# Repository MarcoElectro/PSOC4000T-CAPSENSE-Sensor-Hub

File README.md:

# PSOC4000T-CAPSENSE-Sensor-Hub
An simple way to use capacitive sensors in combination with Infineon's CAPSENSE technology.

# Setup
After the PCB is soldered, the Rasperry Pi Pico needs to be connected as follows:
| Raspberry Pi Pico 2W Pin | Connection | Function |
|-----------------------|-----------------------|----------|
| GPIO2 (Pin 4)         | SDA (Sensor Hub)                | I2C Data |
| GPIO3 (Pin 5)         | SCL (Sensor Hub)                   | I2C Clock |
| GPIO28 (Pin 34)       | VCC (Sensor Hub)                  | Power Supply (3.3V) |
| GND (Pin 3 or 38)     | GND (Sensor Hub / BME280)                  | Ground |
| GPIO4 (Pin 6)         | BME280 SDA            | Environmental Sensor Data |
| GPIO5 (Pin 7)         | BME280 SCL 

# PicoLogger
For obtaining the CAPSENSE data from the Sensor Hub, the PicoLogger can be controlled over an web interface. 
Connect to the AP of the PicoLogger and call following pages:

- Main page: http://192.168.4.1
- Status page:  http://192.168.4.1/status

On the status page, the current state is shown e.g IDLE or the running data collection.

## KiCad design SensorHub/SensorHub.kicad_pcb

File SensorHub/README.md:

# KiCad Project for Sensor Hub PCB
The PCB conists of an PSOC4000T and a few additional components,
making the board a simple and cheap option to use Infineon`s CAPSENSE technology for capacitive sensors.

For programming an SWD Programmer is needed. 
I used the MiniProg4 (CY8CKIT-005-A).

Soldering the PSOC4000T is easy using solder paste and a heat plate or air soldering station.

Feel free to improve the layout and update it to your needs.

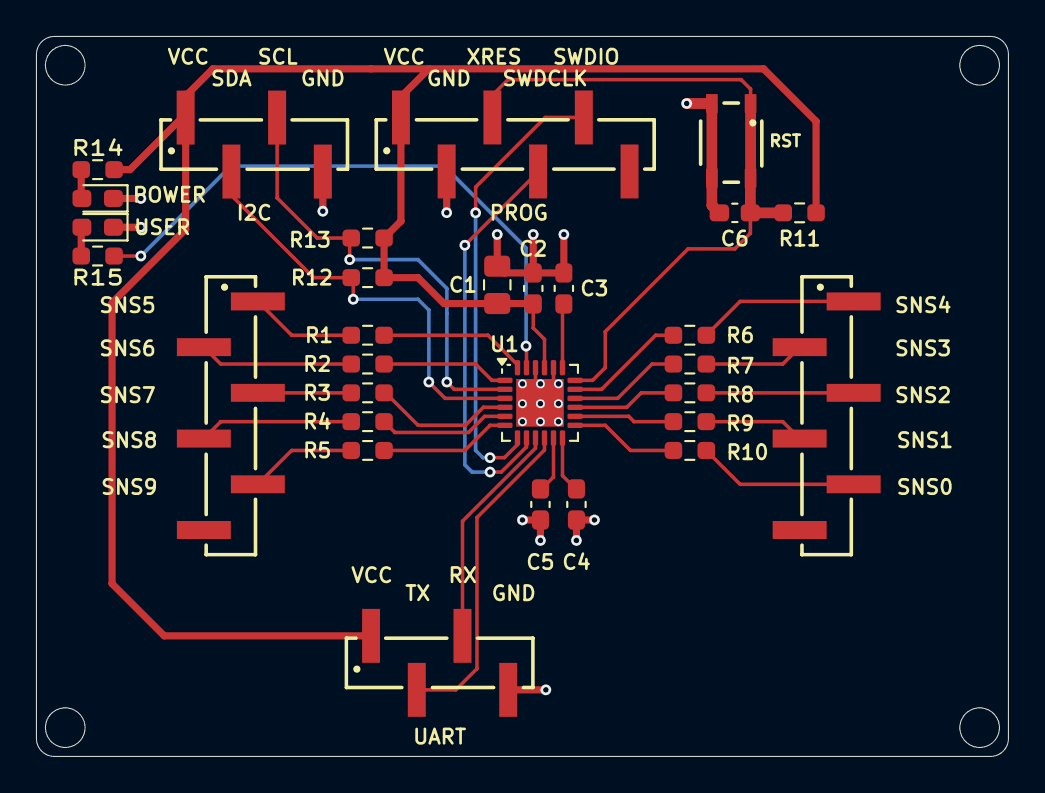
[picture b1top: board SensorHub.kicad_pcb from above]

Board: 2 copper layers, 54.0 x 40.0 mm, 30 parts (0 on the bottom side), 35 nets.

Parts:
C1: 4.7 µF; C_0805_2012Metric_Pad1.18x1.45mm_HandSolder
C2: 0.1 µF; C_0603_1608Metric_Pad1.08x0.95mm_HandSolder
C3: 2.2 µF; C_0603_1608Metric_Pad1.08x0.95mm_HandSolder
C4, C5: 2.2 nF; C_0603_1608Metric_Pad1.08x0.95mm_HandSolder
C6: 0.1µF; C_0603_1608Metric_Pad1.08x0.95mm_HandSolder
I2C: I2C; 61000418321_5pins
J1: CS1; 61000618321_6pins
J2: CS2; 61000618321_6pins
POWER: POWER; LED_0603_1608Metric_Pad1.05x0.95mm_HandSolder
PROG: SWD; 61000618321_6pins
R1, R2, R3, R4, R5, R6, R7, R8, R9, R10, R14: 560R; R_0603_1608Metric_Pad0.98x0.95mm_HandSolder
R11, R12, R13, R15: 4k7; R_0603_1608Metric_Pad0.98x0.95mm_HandSolder
RST: RESET; 434133025816
U1: CY8C4046LQI-T452; QFN-24-1EP_4x4mm_P0.5mm_EP2.65x2.65mm
UART: UART; 61000418321_5pins
USER: USER; LED_0603_1608Metric_Pad1.05x0.95mm_HandSolder

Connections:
/SCL: I2C.3, R13.2, U1.2 (P2.2)
/SDA: I2C.2, R12.2, U1.3 (P2.3)
/SNS0: R10.1, U1.13 (P0.0)
/SNS1: R9.1, U1.14 (P0.1)
/SNS2: R8.1, U1.15 (P0.2)
/SNS3: R7.1, U1.16 (P0.3)
/SNS4: R6.1, U1.17 (EXTCLK_P0.4)
/SNS5: R1.1, U1.24 (P2.0)
/SNS6: R2.1, U1.1 (P2.1)
/SNS7: R3.1, U1.4 (P2.4)
/SNS8: R4.1, U1.5 (P2.5)
/SNS9: R5.1, U1.6 (P3.0)
/SWDCLK: PROG.4, U1.8 (SWDCLK_P3.3)
/SWDIO: PROG.5, U1.7 (SWDIO_P3.2)
/UART_RX: U1.9 (P4.0), UART.3
/UART_TX: U1.10 (P4.1), UART.2
/USER_LED: R15.1, U1.23 (P1.0)
/XRES: C6.1, PROG.3, R11.2, RST.1, RST.2, U1.18 (XRES)
GND: C1.2, C2.2, C3.2, C4.2, C5.2, C6.2, I2C.4, POWER.1 (K), PROG.2, RST.3, RST.4, U1.20 (VSSD), U1.22 (VSSA), U1.25 (VSS), UART.4, USER.1 (K)
unnamed: POWER.2 (A), R14.2
unnamed: R15.2, USER.2 (A)
unnamed: J1.1, R1.2
unnamed: J1.2, R2.2
unnamed: J1.3, R3.2
unnamed: J1.4, R4.2
unnamed: J1.5, R5.2
unnamed: J2.1, R6.2
unnamed: J2.2, R7.2
unnamed: J2.3, R8.2
unnamed: J2.4, R9.2
unnamed: J2.5, R10.2
unnamed: C5.1, U1.11 (CMOD1_P4.2)
unnamed: C4.1, U1.12 (CMOD2_P4.3)
unnamed: C3.1, U1.19 (VCCD)
VCC: C1.1, C2.1, I2C.1, PROG.1, R11.1, R12.1, R13.1, R14.1, U1.21 (VDDD), UART.1

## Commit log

2025-10-08 Init push
2025-10-09 Images
